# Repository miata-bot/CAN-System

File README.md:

# Miata CAN System

## Useful Links

* [Gerber Generation for PCBWay](https://www.pcbway.com/blog/help_center/Generate_Gerber_file_from_Kicad.html)
* [Position Generation for PCBWay](https://www.pcbway.com/blog/help_center/Generate_Position_File_in_Kicad.html)

## Underglow Controller

## Headlight Controller

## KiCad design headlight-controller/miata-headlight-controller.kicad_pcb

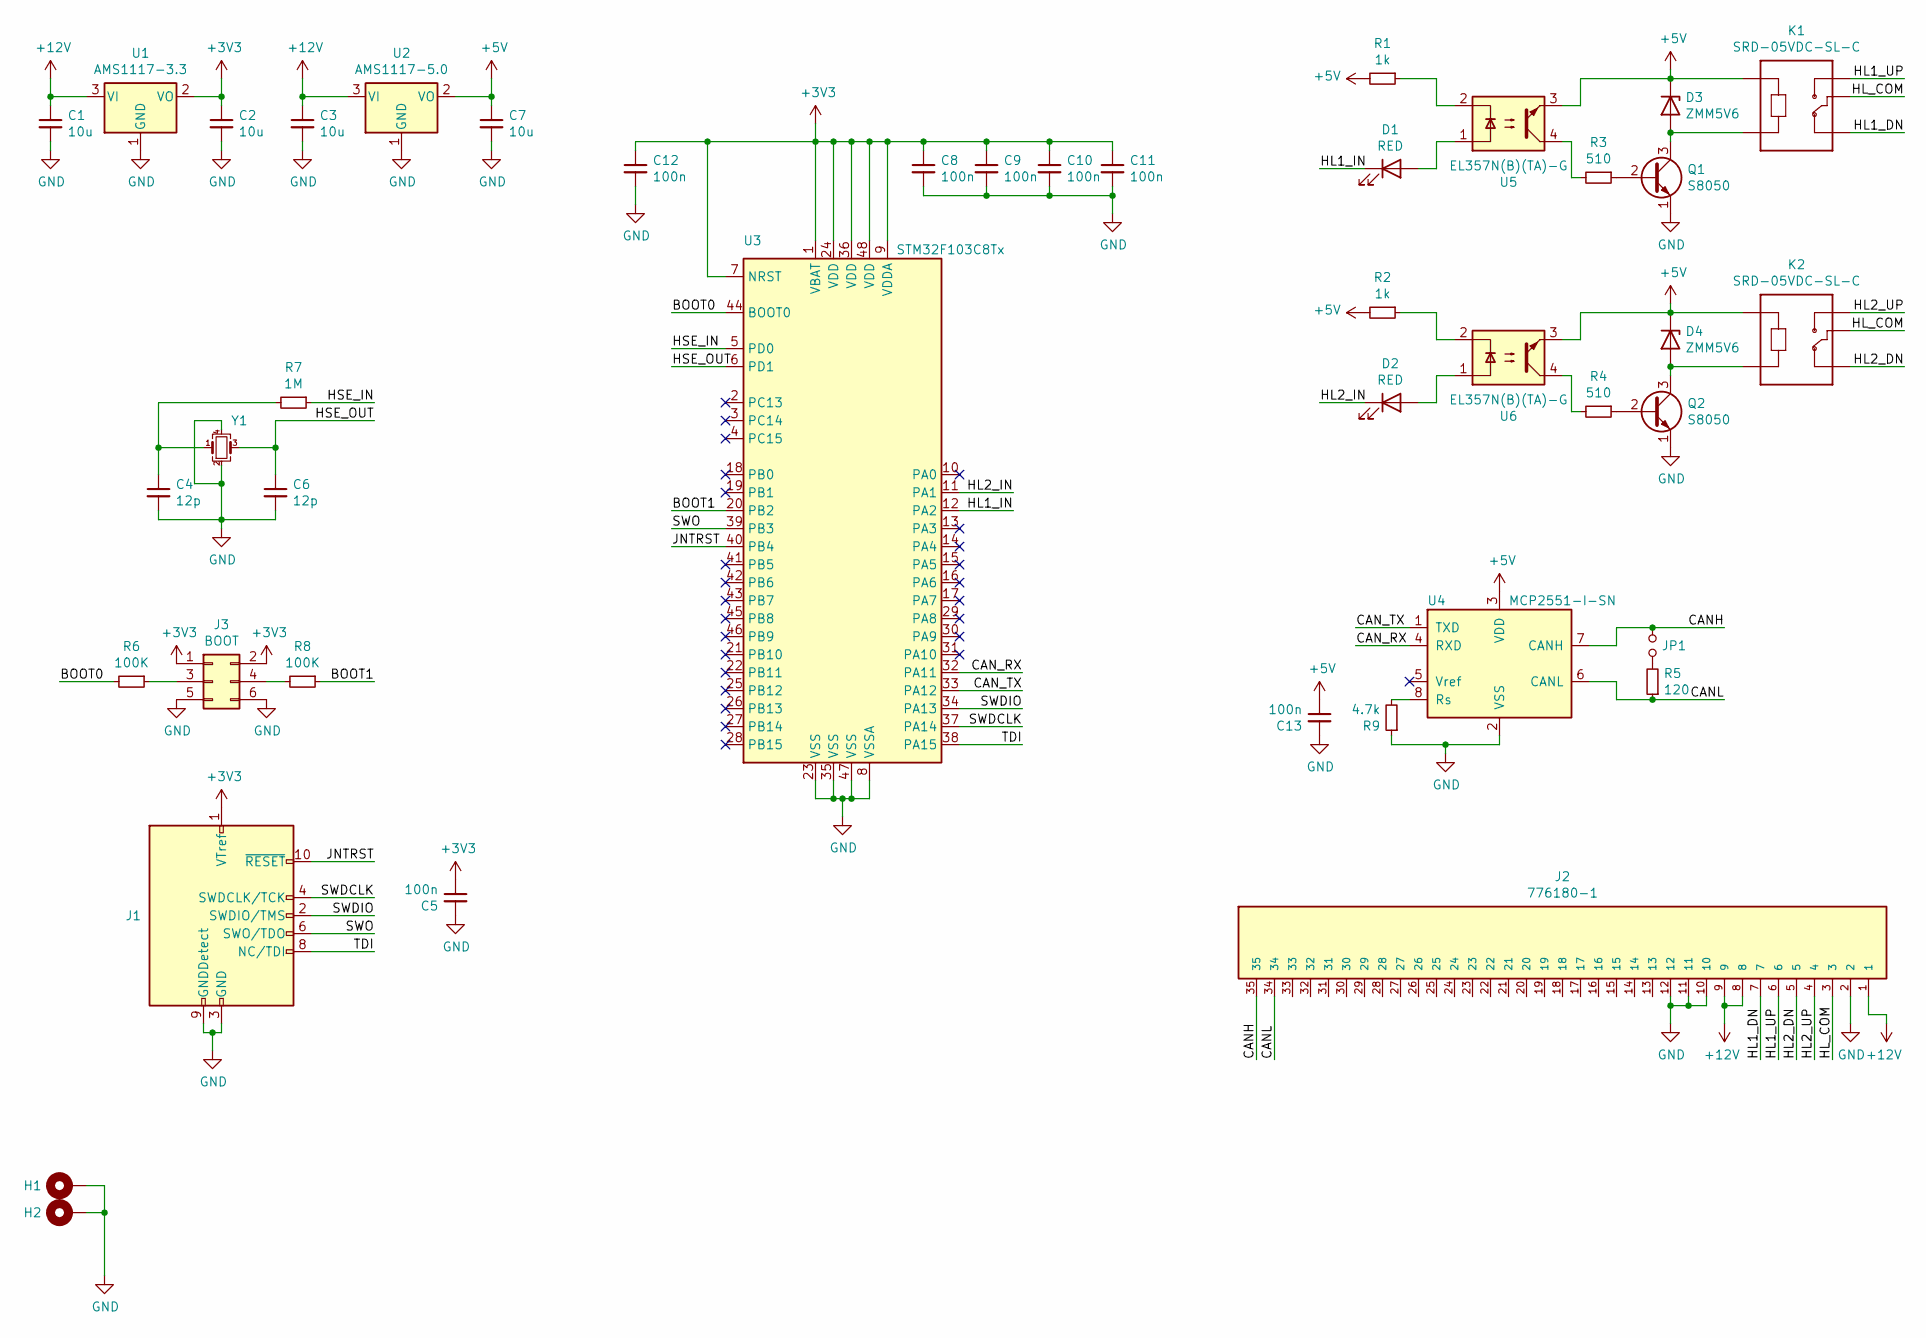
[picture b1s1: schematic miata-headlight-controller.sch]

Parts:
C1, C2, C3, C7: 10u; CP_EIA-3216-18_Kemet-A; Manufacturer Part # TAJA106K016RNJ; LCSC_PN C7171
C4, C6: 12p; C_0402_1005Metric
C5, C8, C9, C10, C11, C12, C13: 100n; C_0402_1005Metric; Manufacturer Part # CL05B104KO5NNNC; LCSC_PN C1525
D1, D2: RED; LED_0805_2012Metric; Manufacturer Part # NCD0805R1; LCSC_PN C84256
D3, D4: ZMM5V6; D_MiniMELF; Manufacturer Part # ZMM5V6; LCSC_PN C8062
H1, H2: MountingHole_Pad; MountingHole_3mm_Pad_Via
J1: Conn_ARM_JTAG_SWD_10; 20021221-00010C4LF
J2: 776180-1; TE_776180-1
J3: BOOT; PinHeader_2x03_P2.54mm_Vertical
JP1: Jumper_NO_Small; SolderJumper-2_P1.3mm_Open_RoundedPad1.0x1.5mm
K1, K2: SRD-05VDC-SL-C; RELAY_SRD-05VDC-SL-C; Manufacturer Part # SRD-05VDC-SL-C; LCSC_PN C35449
Q1, Q2: S8050; SOT-23; Manufacturer Part # SS8050; LCSC_PN C2150
R1, R2: 1k; R_0805_2012Metric; Manufacturer Part # 0805W8F1001T5E; LCSC_PN C17513
R3, R4: 510; R_0805_2012Metric; Manufacturer Part # 0805W8F5100T5E; LCSC_PN C17734
R5: 120; R_1206_3216Metric; Manufacturer Part # 1206W4F1204T5E; LCSC_PN C22107
R6, R8: 100K; R_0402_1005Metric
R7: 1M; R_0402_1005Metric
R9: 4.7k; R_0402_1005Metric
U1: AMS1117-3.3; SOT-223-3_TabPin2; Manufacturer Part # AMS1117-3.3; LCSC_PN C6186
U2: AMS1117-5.0; SOT-223-3_TabPin2; Manufacturer Part # AMS1117-5.0; LCSC_PN C6187
U3: STM32F103C8Tx; LQFP-48_7x7mm_P0.5mm; LCSC_PN C8734
U4: MCP2551-I-SN; SOIC-8_3.9x4.9mm_P1.27mm; LCSC_PN C7376
U5, U6: EL357N(B)(TA)-G; SOP-4_4.1x4.4mm_P2.54mm; Manufacturer Part # EL357N(B)(TA)-G; LCSC_PN C6649
Y1: Crystal_GND24_Small; Crystal_SMD_3225-4Pin_3.2x2.5mm

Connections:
+3V3: C2.1, C5.1, C8.1, C9.1, C10.1, C11.1, C12.1, J1.1 (VTref), J3.1, J3.2, U1.2 (VO), U3.1 (VBAT), U3.7 (NRST), U3.9 (VDDA), U3.24 (VDD), U3.36 (VDD), U3.48 (VDD)
+5V: C7.1, C13.1, D3.1 (K), D4.1 (K), K1.A1, K2.A1, R1.2, R2.2, U2.2 (VO), U4.3 (VDD), U5.3, U6.3
+12V: C1.1, C3.1, J2.1, J2.8, J2.9, U1.3 (VI), U2.3 (VI)
/BOOT0: R6.2, U3.44 (BOOT0)
/BOOT1: R8.1, U3.20 (PB2)
/CANH: J2.35, JP1.1, U4.7 (CANH)
/CANL: J2.34, R5.1, U4.6 (CANL)
/CAN_RX: U3.32 (PA11), U4.4 (RXD)
/CAN_TX: U3.33 (PA12), U4.1 (TXD)
/HL1_DN: J2.7, K1.NC
/HL1_IN: D1.1 (K), U3.12 (PA2)
/HL1_UP: J2.6, K1.NO
/HL2_DN: J2.5, K2.NC
/HL2_IN: D2.1 (K), U3.11 (PA1)
/HL2_UP: J2.4, K2.NO
/HL_COM: J2.3, K1.COM, K2.COM
/HSE_IN: R7.1, U3.5 (PD0)
/HSE_OUT: C6.1, U3.6 (PD1), Y1.3
/JNTRST: J1.10 (~RESET~), U3.40 (PB4)
/SWDCLK: J1.4 (SWDCLK/TCK), U3.37 (PA14)
/SWDIO: J1.2 (SWDIO/TMS), U3.34 (PA13)
/SWO: J1.6 (SWO/TDO), U3.39 (PB3)
/TDI: J1.8 (NC/TDI), U3.38 (PA15)
GND: C1.2, C2.2, C3.2, C4.2, C5.2, C6.2, C7.2, C8.2, C9.2, C10.2, C11.2, C12.2, C13.2, H1.1, H2.1, J1.3 (GND), J1.5 (GND), J1.9 (GNDDetect), J2.2, J2.10, J2.11, J2.12, J3.5, J3.6, Q1.1 (E), Q2.1 (E), R9.1, U1.1 (GND), U2.1 (GND), U3.8 (VSSA), U3.23 (VSS), U3.35 (VSS), U3.47 (VSS), U4.2 (VSS), Y1.2, Y1.4
unnamed: C4.1, R7.2, Y1.1
unnamed: D1.2 (A), U5.1
unnamed: D2.2 (A), U6.1
unnamed: D3.2 (A), K1.A2, Q1.3 (C)
unnamed: D4.2 (A), K2.A2, Q2.3 (C)
unnamed: J3.3, R6.1
unnamed: J3.4, R8.2
unnamed: JP1.2, R5.2
unnamed: Q1.2 (B), R3.1
unnamed: Q2.2 (B), R4.1
unnamed: R1.1, U5.2
unnamed: R2.1, U6.2
unnamed: R3.2, U5.4
unnamed: R4.2, U6.4
unnamed: R9.2, U4.8 (Rs)

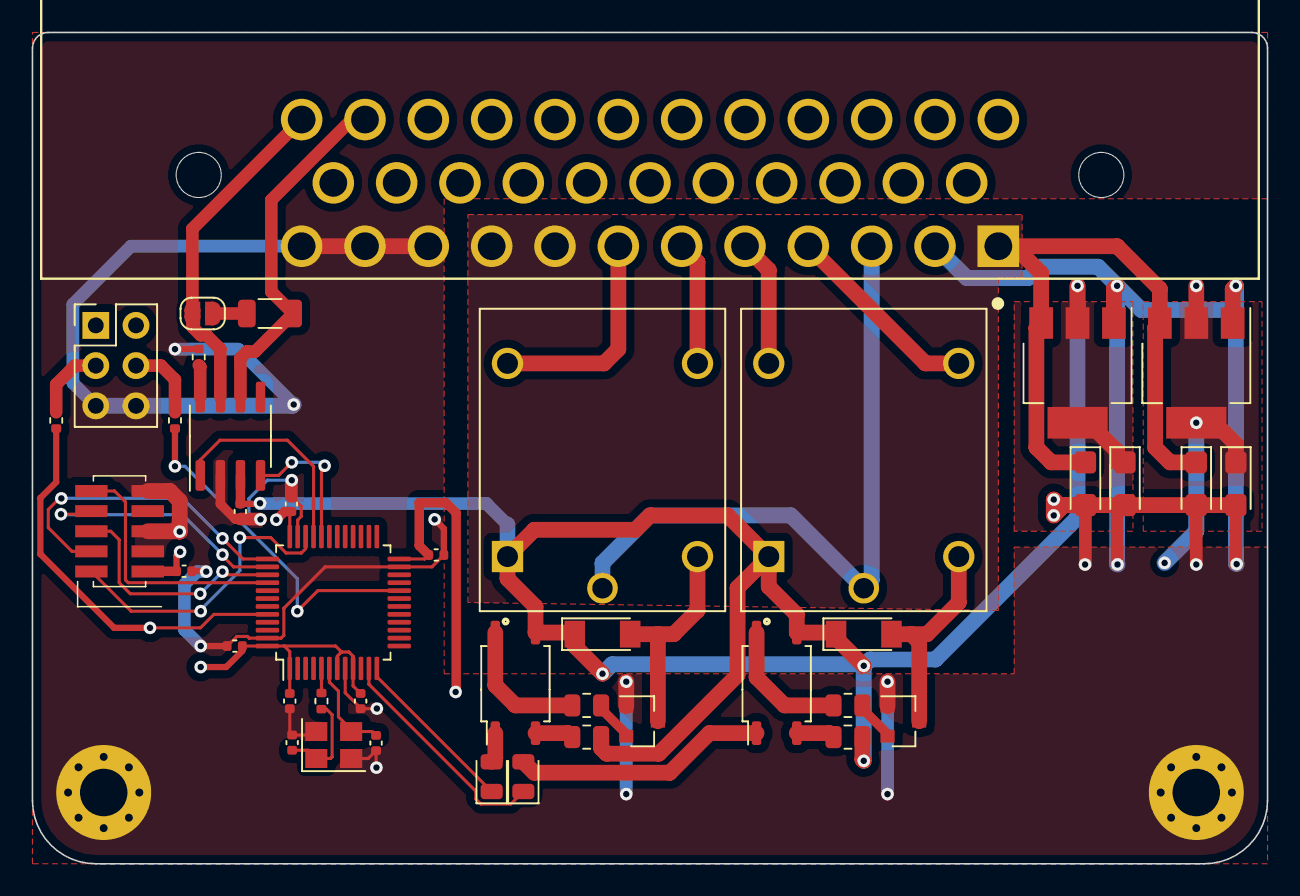
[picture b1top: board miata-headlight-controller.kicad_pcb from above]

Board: 2 copper layers, 78.0 x 52.5 mm, 43 parts (0 on the bottom side), 39 nets.

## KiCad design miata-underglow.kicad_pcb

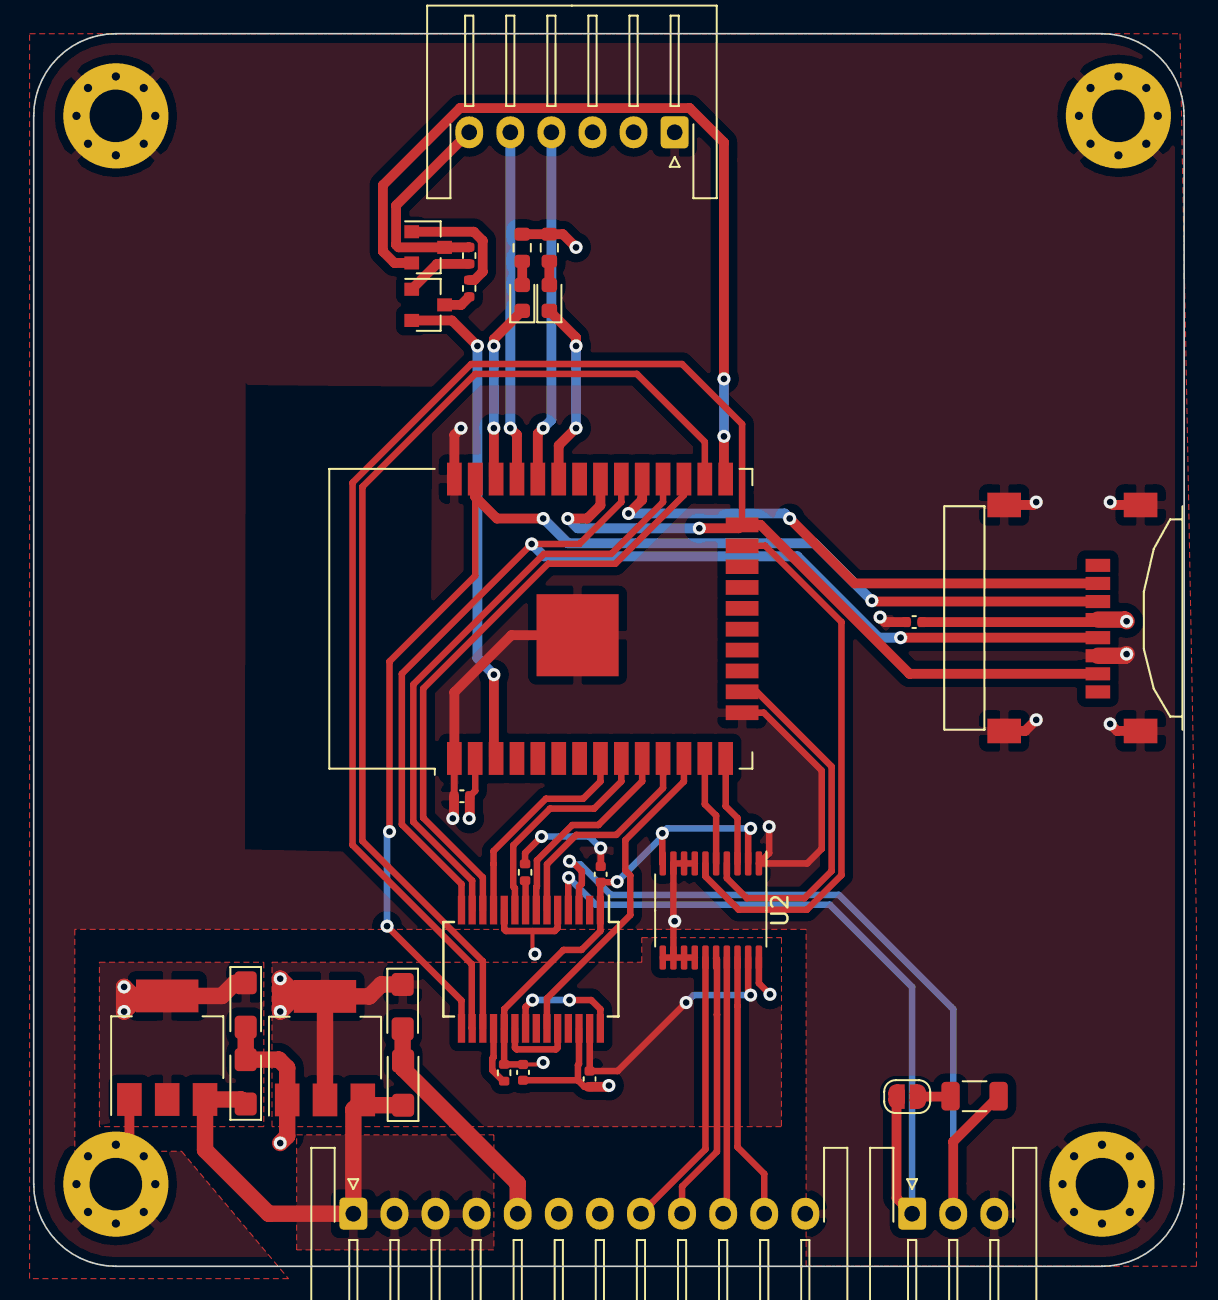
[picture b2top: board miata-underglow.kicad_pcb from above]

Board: 4 copper layers, 70.0 x 75.0 mm, 34 parts (0 on the bottom side), 43 nets.

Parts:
C1, C2, C3, C4: 10u; CP_EIA-3216-18_Kemet-A
C5, C6, C7, C8, C9: 100n; C_0402_1005Metric
D1, D2: LED_Small; LED_0603_1608Metric
H1, H2, H3, H4: MountingHole_Pad; MountingHole_3.2mm_M3_Pad_Via
J1: Micro_SD_Card; MOLEX_47219-2001
J2: FTDI; JST_XH_S6B-XH-A-1_1x06_P2.50mm_Horizontal
J3: LEDS; JST_XH_S12B-XH-A-1_1x12_P2.50mm_Horizontal
J4: CAN; JST_XH_S3B-XH-A-1_1x03_P2.50mm_Horizontal
JP1: Jumper_NO_Small; SolderJumper-2_P1.3mm_Open_RoundedPad1.0x1.5mm
Q1, Q2: SS8050; SOT-23
R1, R2, R5, R6: 10k; R_0402_1005Metric
R3, R4: R_Small; R_0603_1608Metric
R7: 120; R_1206_3216Metric
U1: AMS1117-3.3; SOT-223-3_TabPin2
U2: TXS0108EPW; TSSOP-20_4.4x6.5mm_P0.65mm
U3: AMS1117-5.0; SOT-223-3_TabPin2
U4: ESP32-WROOM-32D; ESP32-WROOM-32
U5: MCP25625-x-SS; SSOP-28_5.3x10.2mm_P0.65mm

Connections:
+3V3: C2.1, C5.2, C6.2, C7.2, C8.2, J1.4, R3.1, R4.1, R5.2, U1.2, U2.2, U2.10, U4.2, U5.1, U5.19
+5V: C4.1, C9.2, U2.19, U3.2, U5.27
+12V: C1.1, C3.1, J3.1, J3.2, J3.3, J3.4, U1.3, U3.3
/CANH: J4.1, JP1.1, U5.4
/CANL: J4.2, R7.2, U5.3
/CAN_INT: U4.28, U5.13
/CAN_RX0_BF: U4.27, U5.12
/CAN_RX1_BF: U4.8, U5.11
/CAN_TX0_RTS: U4.12, U5.23
/CAN_TX1_RTS: U4.11, U5.6
/CAN_TX2_RTS: U4.10, U5.7
/FTDI_DTR: J2.6, Q2.3, R1.2
/FTDI_RTS: Q1.3, R2.2
/FTDI_RX: J2.5, U4.35
/FTDI_TX: J2.4, U4.34
/GPIO0: Q2.2, U4.25
/LED0: U2.4, U4.16
/LED0_OUT: J3.10, U2.17
/LED1: U2.3, U4.14
/LED1_OUT: J3.11, U2.18
/LED2: U2.5, U4.13
/LED2_OUT: J3.9, U2.16
/LED3: U2.6, U4.23
/LED3_OUT: J3.8, U2.15
/RESET: Q1.2, U4.3
/SD_CLK: J1.5, U4.30, U5.14
/SD_CMD: J1.3, U4.37, U5.15
/SD_D0: J1.7, U4.24, U4.31, U5.16
/SD_D3: J1.2, U4.29
/SPI_CS: U4.26, U5.17
/STATUS0: D1.1, U4.33
/STATUS1: D2.1, U4.36
/XTAL_OUT: U4.9, U5.9
GND: C1.2, C2.2, C3.2, C4.2, C5.1, C6.1, C7.1, C8.1, C9.1, H1.1, H2.1, H3.1, H4.1, J1.6, J1.G1, J1.G2, J1.G3, J1.G4, J2.1, J3.5, J3.6, J3.7, J3.12, J4.3, R6.2, U1.1, U2.1, U2.7, U2.8, U2.9, U2.11, U2.12, U2.13, U2.14, U2.20, U3.1, U4.1, U4.15, U4.38, U4.39, U5.5, U5.10, U5.26
unnamed: D1.2, R3.2
unnamed: D2.2, R4.2
unnamed: JP1.2, R7.1
unnamed: Q1.1, R1.1
unnamed: Q2.1, R2.1
unnamed: R5.1, U5.18
unnamed: R6.1, U5.8
unnamed: U5.20, U5.24
unnamed: U5.21, U5.28

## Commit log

2021-07-07 Progress on routing
2021-07-08 More routing progress
2021-07-08 p much complete i think
2021-07-08 Hardware Rev A
2021-07-08 Add Second controller for Headlights
2021-07-09 Restructure project
2021-07-09 Add gitattributes file for fixing language reporting
2021-07-09 Add 3d render
2021-07-09 Add more 3d models
2022-03-17 Add new underglow controller
